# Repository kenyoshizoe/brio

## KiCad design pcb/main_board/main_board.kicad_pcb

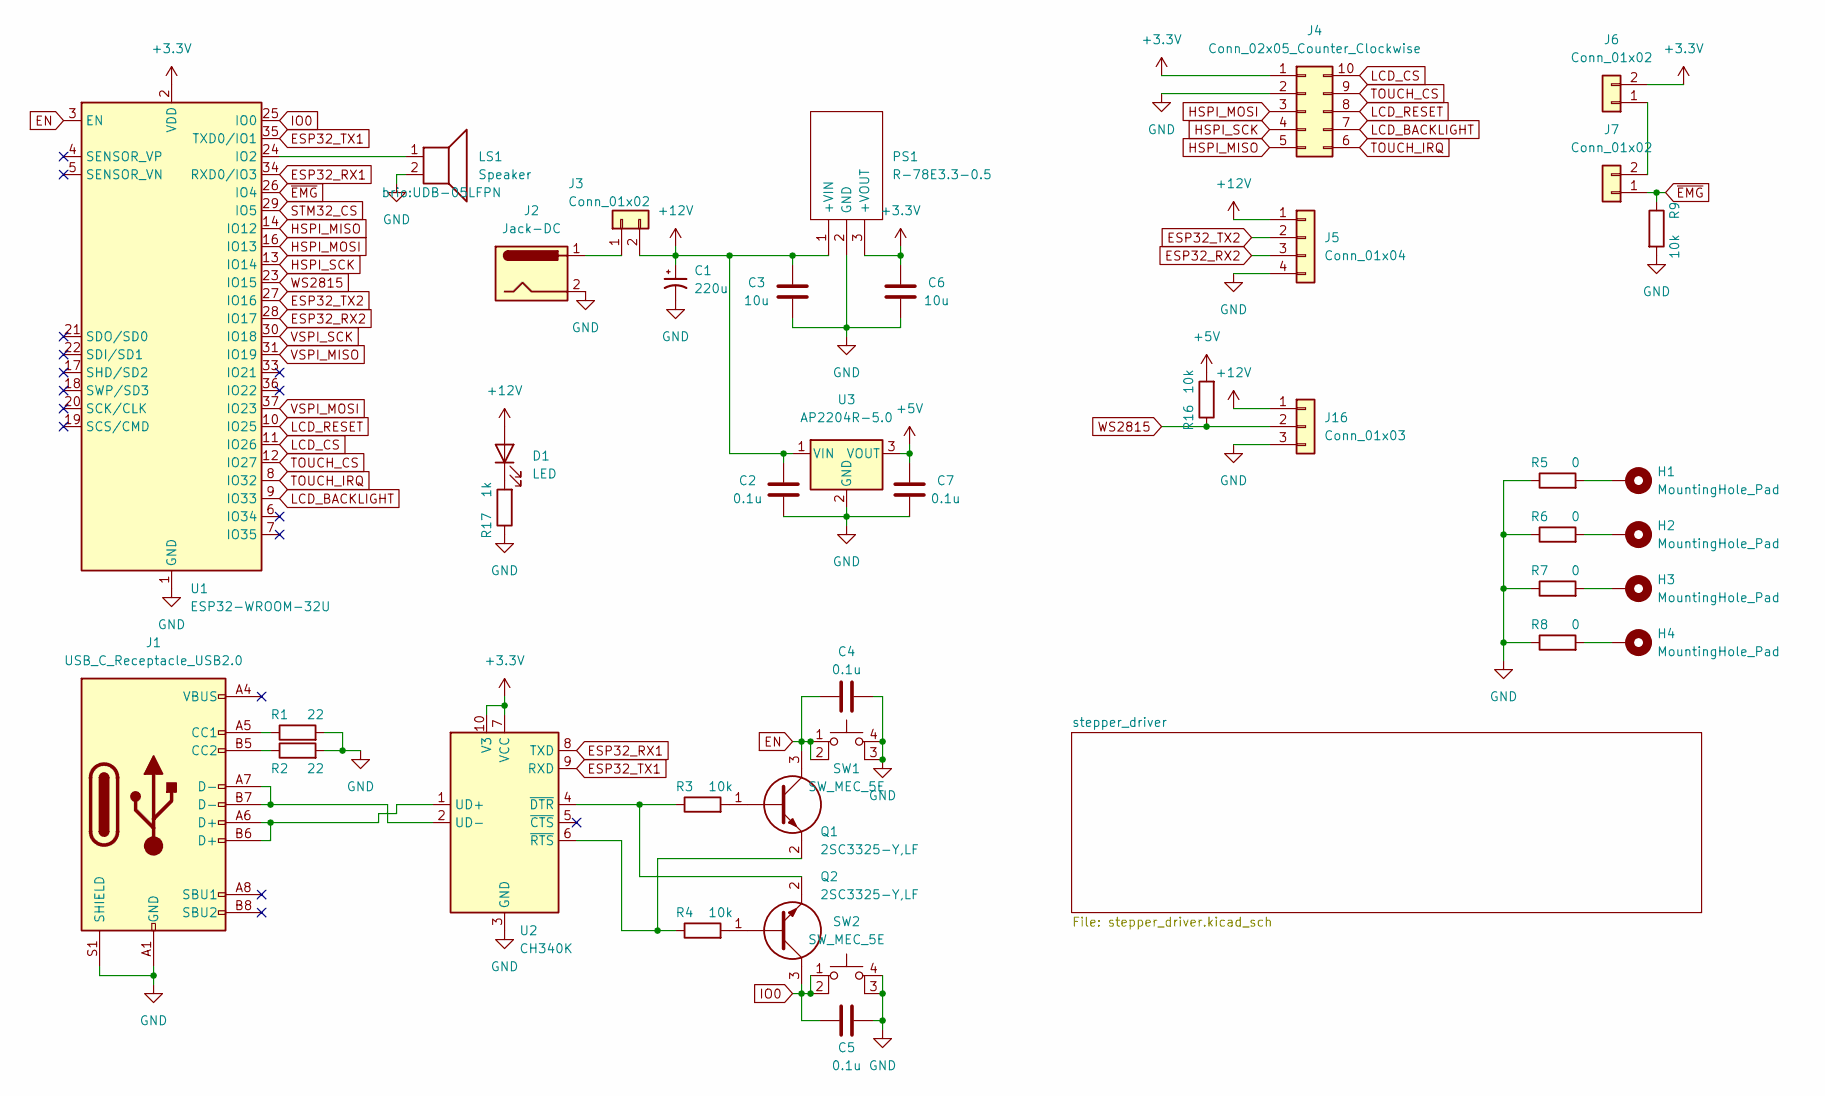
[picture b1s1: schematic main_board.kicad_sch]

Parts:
C1: 220u; CP_Elec_8x10
C2, C4, C5, C7: 0.1u; C_0603_1608Metric_Pad1.08x0.95mm_HandSolder
C3, C6: 10u; C_0603_1608Metric_Pad1.08x0.95mm_HandSolder
D1: LED; LED_0603_1608Metric_Pad1.05x0.95mm_HandSolder
H1, H2, H3, H4: MountingHole_Pad; MountingHole_3.2mm_M3_Pad_Via
J1: USB_C_Receptacle_USB2.0; USB_C_Receptacle_XKB_U262-16XN-4BVC11
J2: Jack-DC; 2DC-G213-D42
J3: Conn_01x02; JST_VH_B2P-VH_1x02_P3.96mm_Vertical
J4: Conn_02x05_Counter_Clockwise; PinHeader_2x05_P2.54mm_Vertical
J5: Conn_01x04; JST_PH_B4B-PH-K_1x04_P2.00mm_Vertical
J6: Conn_01x02; PinHeader_1x02_P2.54mm_Vertical
J7: Conn_01x02; PinHeader_1x02_P2.54mm_Horizontal
J16: Conn_01x03; JST_VH_B3P-VH_1x03_P3.96mm_Vertical
LS1: Speaker; UDB-05LFPN
PS1: R-78E3.3-0.5; R78E1205; Mouser Part Number 919-R-78E3.3-0.5
Q1, Q2: 2SC3325-Y,LF; 2SC3325YLF; Mouser Part Number 757-2SC3325-YLF
R1, R2: 22; R_0603_1608Metric_Pad0.98x0.95mm_HandSolder
R3, R4, R9, R16: 10k; R_0603_1608Metric_Pad0.98x0.95mm_HandSolder
R5, R6, R7, R8: 0; R_0603_1608Metric_Pad0.98x0.95mm_HandSolder
R17: 1k; R_0603_1608Metric_Pad0.98x0.95mm_HandSolder
SW1, SW2: SW_MEC_5E; SKRPABE010
U1: ESP32-WROOM-32U
U2: CH340K; SSOP-10_3.9x4.9mm_P1.00mm
U3: AP2204R-5.0; SOT-89-3

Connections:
+3.3V: C6.2, J4.1, J6.2, PS1.3 (+VOUT), U1.2 (VDD), U2.7 (VCC), U2.10 (V3); also elsewhere on the board
+5V: C7.2, R16.2, U3.3 (VOUT)
+12V: C1.1, C2.2, C3.2, D1.2 (A), J3.2, J5.1, J16.1, PS1.1 (+VIN), U3.1 (VIN); also elsewhere on the board
EN: C4.2, Q1.3, SW1.1, SW1.2, U1.3 (EN)
ESP32_RX1: U1.34 (RXD0/IO3), U2.8 (TXD)
ESP32_RX2: J5.3, U1.28 (IO17)
ESP32_TX1: U1.35 (TXD0/IO1), U2.9 (RXD)
ESP32_TX2: J5.2, U1.27 (IO16)
GND: C1.2, C2.1, C3.1, C4.1, C5.1, C6.1, C7.1, J1.A1 (GND), J1.A12 (GND), J1.B1 (GND), J1.B12 (GND), J1.S1 (SHIELD), J2.2, J4.2, J5.4, J16.3, LS1.2, PS1.2 (GND), R1.2, R2.2, R5.1, R6.1, R7.1, R8.1, R9.2, R17.1, SW1.3 (K), SW1.4 (A), SW2.3 (K), SW2.4 (A), U1.1 (GND), U1.15 (GND), U1.38 (GND), U1.39 (GND), U2.3 (GND), U3.2 (GND); also elsewhere on the board
HSPI_MISO: J4.5, U1.14 (IO12)
HSPI_MOSI: J4.3, U1.16 (IO13)
HSPI_SCK: J4.4, U1.13 (IO14)
IO0: C5.2, Q2.3, SW2.1, SW2.2, U1.25 (IO0)
LCD_BACKLIGHT: J4.7, U1.9 (IO33)
LCD_CS: J4.10, U1.11 (IO26)
LCD_RESET: J4.8, U1.10 (IO25)
unnamed: D1.1 (K), R17.2
unnamed: H1.1, R5.2
unnamed: H2.1, R6.2
unnamed: H3.1, R7.2
unnamed: H4.1, R8.2
unnamed: J1.A5 (CC1), R1.1
unnamed: J1.A6 (D+), J1.B6 (D+), U2.1 (UD+)
unnamed: J1.A7 (D-), J1.B7 (D-), U2.2 (UD-)
unnamed: J1.B5 (CC2), R2.1
unnamed: J2.1, J3.1
unnamed: J6.1, J7.2
unnamed: LS1.1, U1.24 (IO2)
unnamed: Q1.1, R3.2
unnamed: Q1.2, R4.1, U2.6 (~RTS)
unnamed: Q2.1, R4.2
unnamed: Q2.2, R3.1, U2.4 (~DTR)
STM32_CS: U1.29 (IO5); also elsewhere on the board
TOUCH_CS: J4.9, U1.12 (IO27)
TOUCH_IRQ: J4.6, U1.8 (IO32)
VSPI_MISO: U1.31 (IO19); also elsewhere on the board
VSPI_MOSI: U1.37 (IO23); also elsewhere on the board
VSPI_SCK: U1.30 (IO18); also elsewhere on the board
WS2815: J16.2, R16.1, U1.23 (IO15)
~EMG: J7.1, R9.1, U1.26 (IO4); also elsewhere on the board

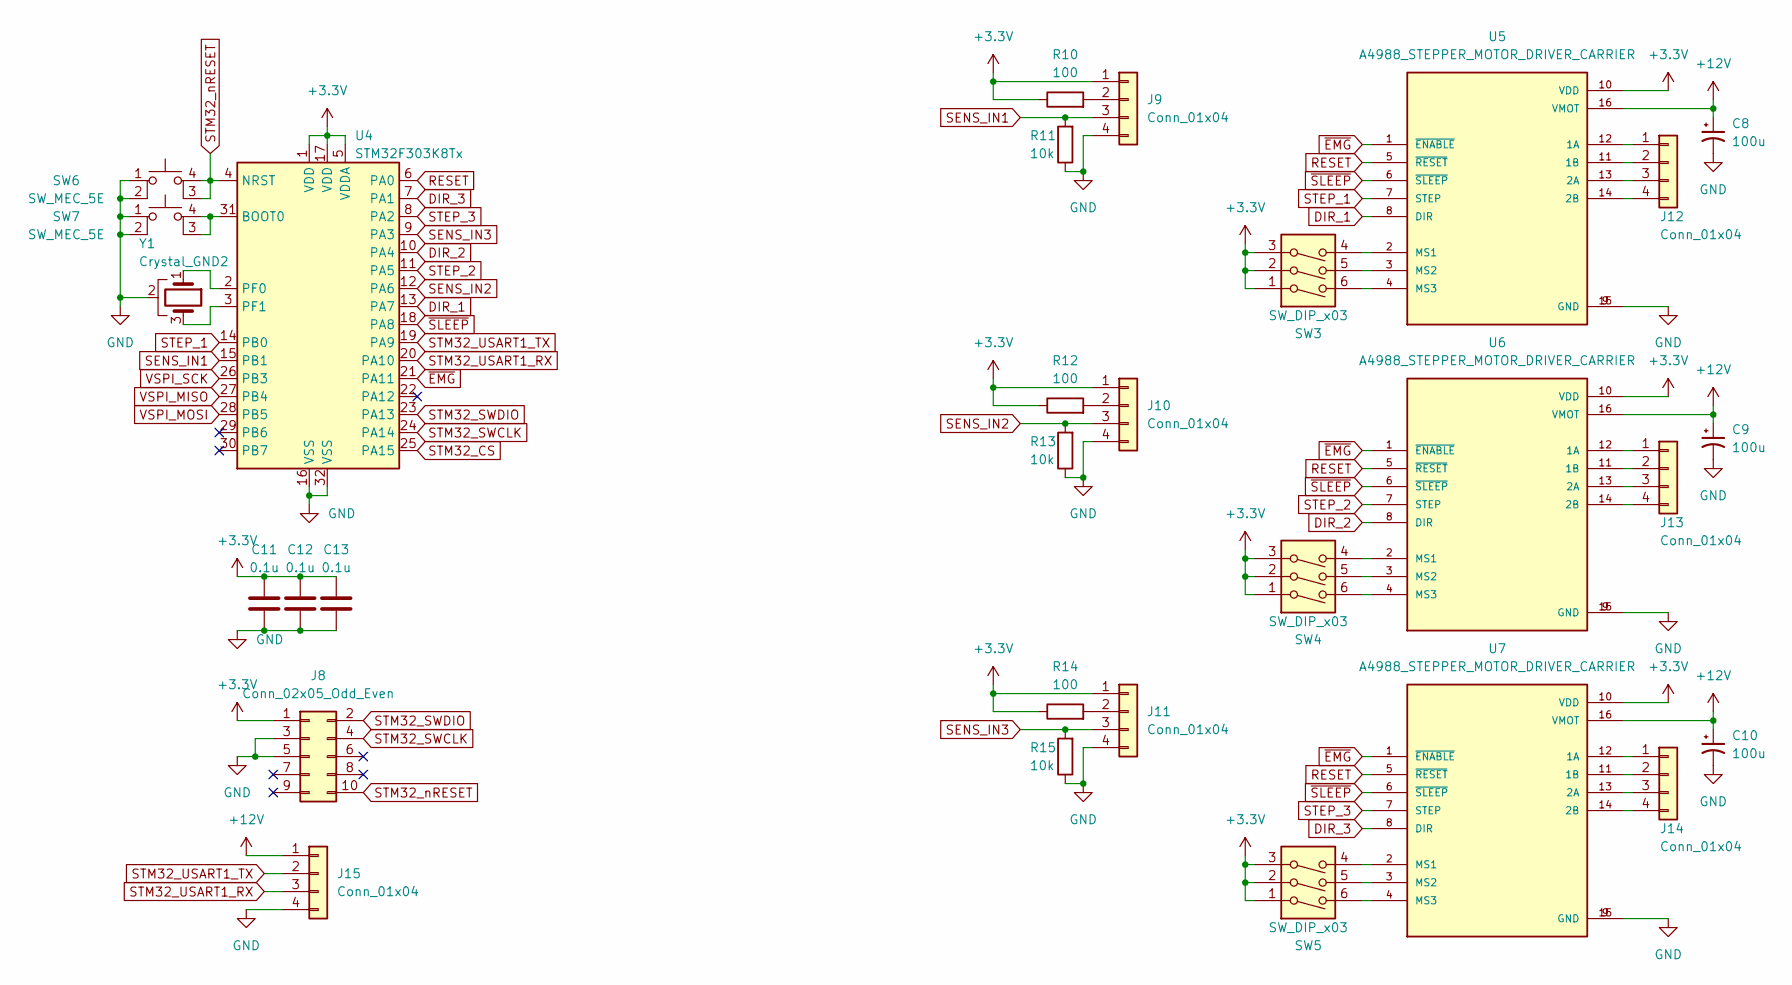
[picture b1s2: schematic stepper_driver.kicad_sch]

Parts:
C8, C9, C10: 100u; CP_Elec_6.3x5.7
C11, C12, C13: 0.1u; C_0603_1608Metric_Pad1.08x0.95mm_HandSolder
J8: Conn_02x05_Odd_Even; PinHeader_2x05_P1.27mm_Vertical
J9, J10, J11: Conn_01x04; JST_XH_B4B-XH-A_1x04_P2.50mm_Vertical
J12, J13, J14: Conn_01x04; JST_VH_B4P-VH_1x04_P3.96mm_Vertical
J15: Conn_01x04; JST_PH_B4B-PH-K_1x04_P2.00mm_Vertical
R10, R12, R14: 100; R_0603_1608Metric_Pad0.98x0.95mm_HandSolder
R11, R13, R15: 10k; R_0603_1608Metric_Pad0.98x0.95mm_HandSolder
SW3, SW4, SW5: SW_DIP_x03; SW_DIP_SPSTx03_Slide_6.7x9.18mm_W7.62mm_P2.54mm_LowProfile
SW6, SW7: SW_MEC_5E; SKRPABE010
U4: STM32F303K8Tx; LQFP-32_7x7mm_P0.8mm
U5, U6, U7: A4988_STEPPER_MOTOR_DRIVER_CARRIER; MODULE_A4988_STEPPER_MOTOR_DRIVER_CARRIER
Y1: Crystal_GND2; Resonator_SMD_Murata_CSTxExxV-3Pin_3.0x1.1mm_HandSoldering

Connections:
+3.3V: C11.2, C12.2, C13.2, J8.1, J9.1, J10.1, J11.1, R10.1, R12.1, R14.1, SW3.1, SW3.2, SW3.3, SW4.1, SW4.2, SW4.3, SW5.1, SW5.2, SW5.3, U4.1 (VDD), U4.5 (VDDA), U4.17 (VDD), U5.10 (VDD), U6.10 (VDD), U7.10 (VDD); also elsewhere on the board
+12V: C8.1, C9.1, C10.1, J15.1, U5.16 (VMOT), U6.16 (VMOT), U7.16 (VMOT); also elsewhere on the board
DIR_1: U4.13 (PA7), U5.8 (DIR)
DIR_2: U4.10 (PA4), U6.8 (DIR)
DIR_3: U4.7 (PA1), U7.8 (DIR)
GND: C8.2, C9.2, C10.2, C11.1, C12.1, C13.1, J8.3, J8.5, J9.4, J10.4, J11.4, J15.4, R11.1, R13.1, R15.1, SW6.1, SW6.2, SW7.1, SW7.2, U4.16 (VSS), U4.32 (VSS), U5.9 (GND), U5.15 (GND), U6.9 (GND), U6.15 (GND), U7.9 (GND), U7.15 (GND), Y1.2; also elsewhere on the board
unnamed: J9.2, R10.2
unnamed: J10.2, R12.2
unnamed: J11.2, R14.2
unnamed: J12.1, U5.12 (1A)
unnamed: J12.2, U5.11 (1B)
unnamed: J12.3, U5.13 (2A)
unnamed: J12.4, U5.14 (2B)
unnamed: J13.1, U6.12 (1A)
unnamed: J13.2, U6.11 (1B)
unnamed: J13.3, U6.13 (2A)
unnamed: J13.4, U6.14 (2B)
unnamed: J14.1, U7.12 (1A)
unnamed: J14.2, U7.11 (1B)
unnamed: J14.3, U7.13 (2A)
unnamed: J14.4, U7.14 (2B)
unnamed: SW3.4, U5.2 (MS1)
unnamed: SW3.5, U5.3 (MS2)
unnamed: SW3.6, U5.4 (MS3)
unnamed: SW4.4, U6.2 (MS1)
unnamed: SW4.5, U6.3 (MS2)
unnamed: SW4.6, U6.4 (MS3)
unnamed: SW5.4, U7.2 (MS1)
unnamed: SW5.5, U7.3 (MS2)
unnamed: SW5.6, U7.4 (MS3)
unnamed: SW7.3 (K), SW7.4 (A), U4.31 (BOOT0)
unnamed: U4.2 (PF0), Y1.1
unnamed: U4.3 (PF1), Y1.3
RESET: U4.6 (PA0), U5.5 (~RESET), U6.5 (~RESET), U7.5 (~RESET)
SENS_IN1: J9.3, R11.2, U4.15 (PB1)
SENS_IN2: J10.3, R13.2, U4.12 (PA6)
SENS_IN3: J11.3, R15.2, U4.9 (PA3)
STEP_1: U4.14 (PB0), U5.7 (STEP)
STEP_2: U4.11 (PA5), U6.7 (STEP)
STEP_3: U4.8 (PA2), U7.7 (STEP)
STM32_CS: U4.25 (PA15); also elsewhere on the board
STM32_SWCLK: J8.4, U4.24 (PA14)
STM32_SWDIO: J8.2, U4.23 (PA13)
STM32_USART1_RX: J15.3, U4.20 (PA10)
STM32_USART1_TX: J15.2, U4.19 (PA9)
STM32_nRESET: J8.10, SW6.3 (K), SW6.4 (A), U4.4 (NRST)
VSPI_MISO: U4.27 (PB4); also elsewhere on the board
VSPI_MOSI: U4.28 (PB5); also elsewhere on the board
VSPI_SCK: U4.26 (PB3); also elsewhere on the board
~EMG: U4.21 (PA11), U5.1 (~ENABLE), U6.1 (~ENABLE), U7.1 (~ENABLE); also elsewhere on the board
~SLEEP: U4.18 (PA8), U5.6 (~SLEEP), U6.6 (~SLEEP), U7.6 (~SLEEP)

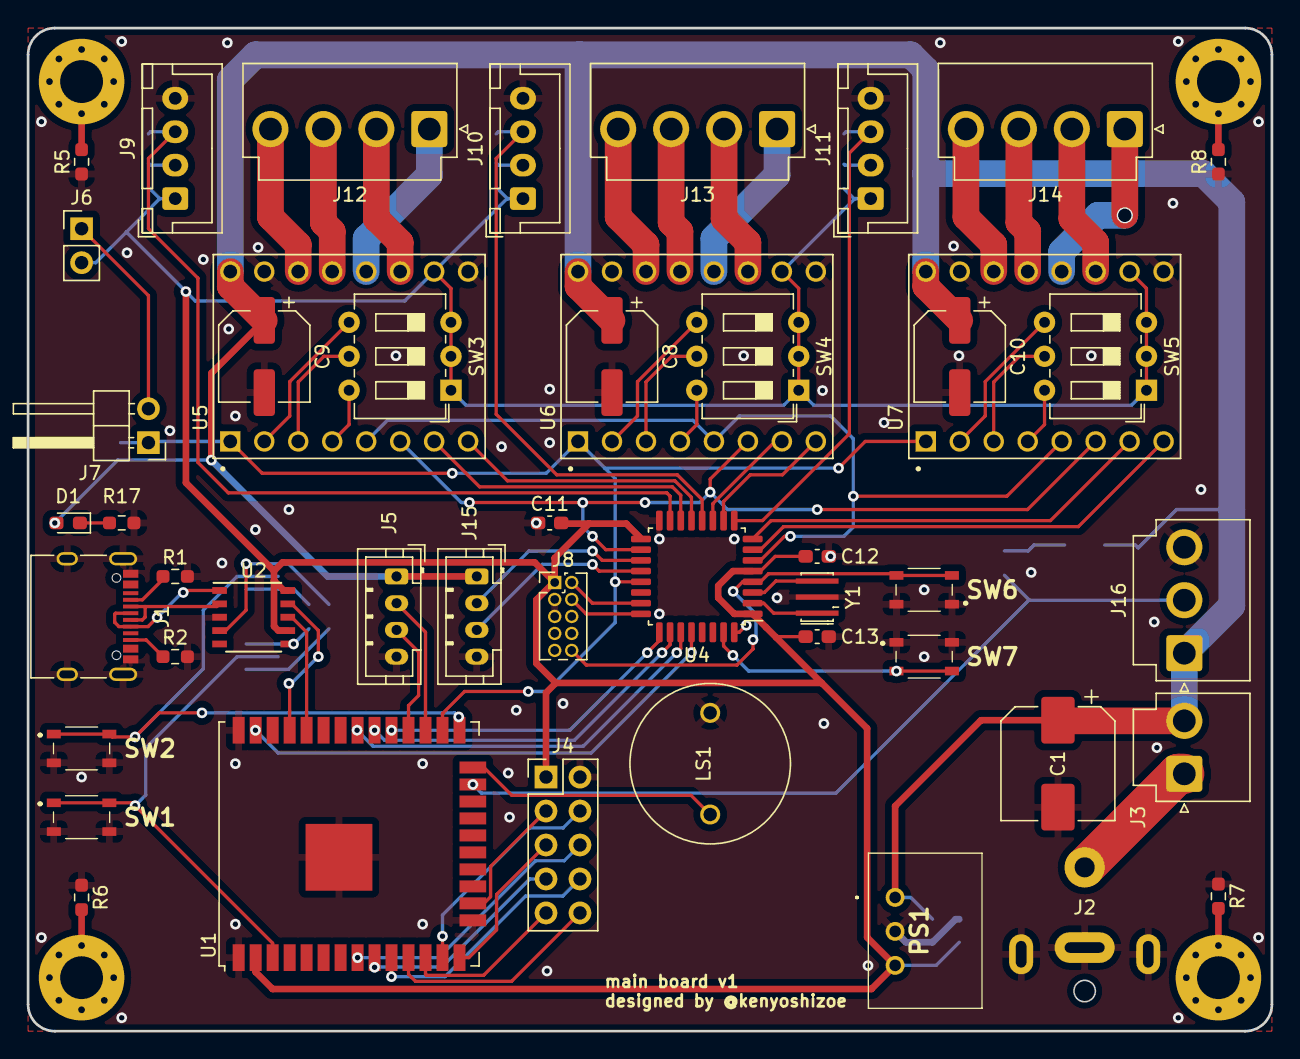
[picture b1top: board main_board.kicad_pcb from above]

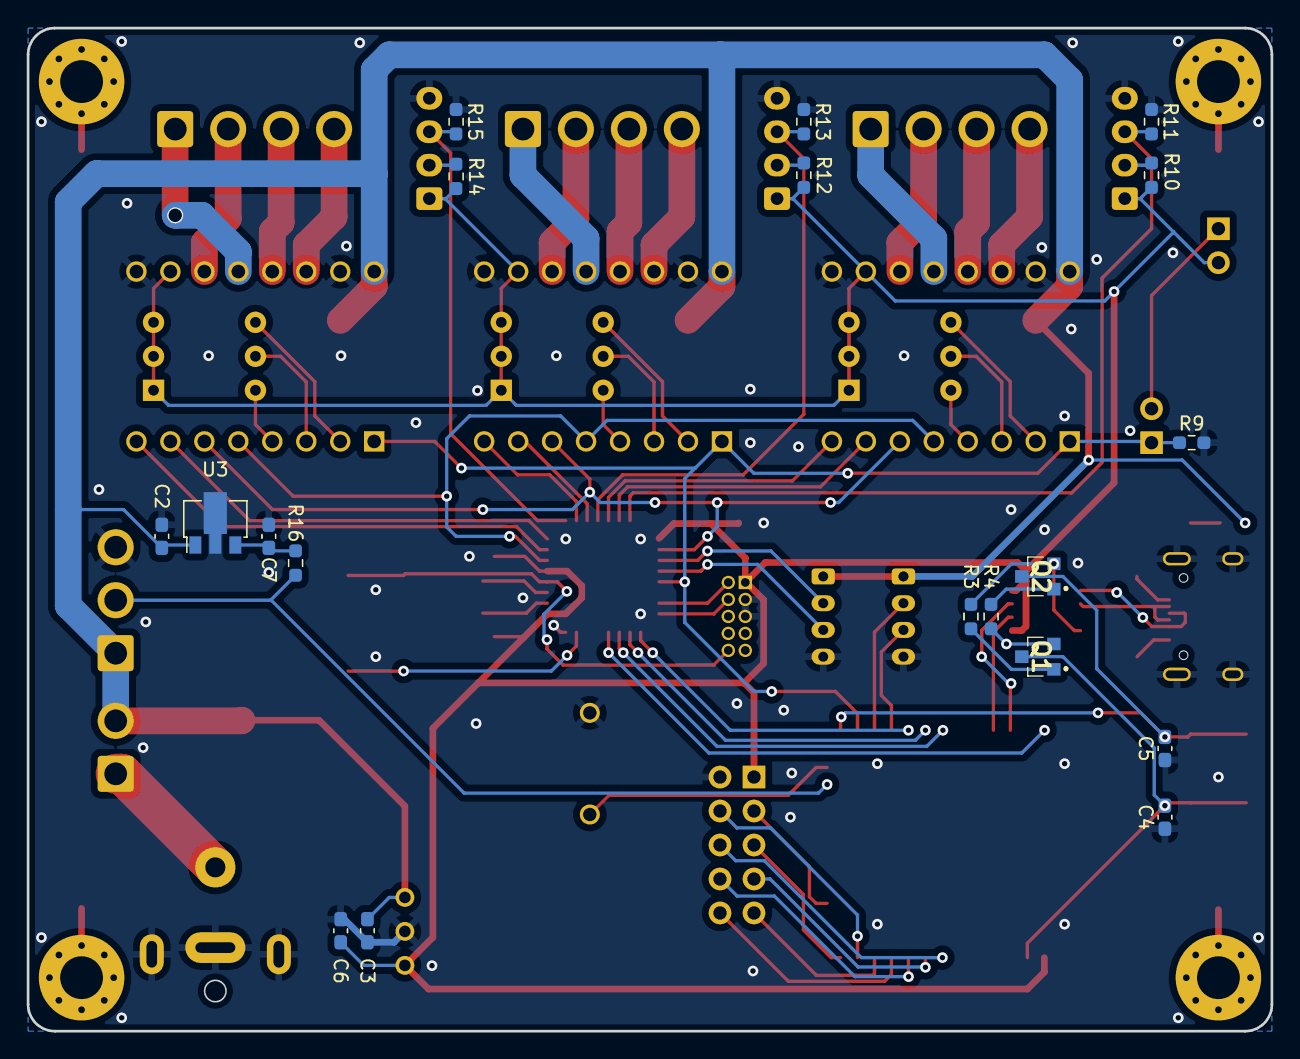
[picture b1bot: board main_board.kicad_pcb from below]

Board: 2 copper layers, 93.0 x 75.0 mm, 70 parts (19 on the bottom side), 83 nets.

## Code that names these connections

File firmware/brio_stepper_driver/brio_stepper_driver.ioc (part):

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Mcu.Name=STM32F303K(6-8)Tx
Mcu.Package=LQFP32
Mcu.UserName=STM32F303K8Tx
PA0.GPIOParameters=GPIO_Label
PA0.GPIO_Label=STEPPER_RESET
PA0.Signal=GPIO_Output
PA1.GPIOParameters=GPIO_Label
PA1.GPIO_Label=STEPPER3_DIR
PA1.Signal=GPIO_Output
PA10.Mode=Asynchronous
PA10.Signal=USART1_RX
PA11.GPIOParameters=GPIO_PuPd,GPIO_Label
PA11.GPIO_Label=STEPPER_EMG
PA11.GPIO_PuPd=GPIO_PULLDOWN
PA11.Signal=GPIO_Input
PA13.Mode=Serial_Wire
PA13.Signal=SYS_JTMS-SWDIO
PA14.Mode=Serial_Wire
PA14.Signal=SYS_JTCK-SWCLK
PA15.Mode=NSS_Signal_Hard_Input
PA15.Signal=SPI1_NSS
PA2.GPIOParameters=GPIO_Label
PA2.GPIO_Label=STEPPER3_STEP
PA2.Signal=S_TIM15_CH1
PA3.GPIOParameters=GPIO_Label
PA3.GPIO_Label=STEPPER3_SENS
PA3.Signal=GPIO_Input
PA4.GPIOParameters=GPIO_Label
PA4.GPIO_Label=STEPPER2_DIR
PA4.Signal=GPIO_Output
PA5.GPIOParameters=GPIO_Label
PA5.GPIO_Label=STEPPER2_STEP
PA5.Signal=S_TIM2_CH1_ETR
PA6.GPIOParameters=GPIO_Label
PA6.GPIO_Label=STEPPER2_SENS
PA6.Signal=GPIO_Input
PA7.GPIOParameters=GPIO_Label
PA7.GPIO_Label=STEPPER1_DIR
PA7.Signal=GPIO_Output
PA8.GPIOParameters=GPIO_Label
PA8.GPIO_Label=STEPPER_SLEEP
PA8.Signal=GPIO_Output
PA9.Mode=Asynchronous
PA9.Signal=USART1_TX
PB0.GPIOParameters=GPIO_Label
PB0.GPIO_Label=STEPPER1_STEP
PB0.Signal=S_TIM3_CH3
PB1.GPIOParameters=GPIO_Label
PB1.GPIO_Label=STEPPER1_SENS
PB1.Signal=GPIO_Input
PB3.Mode=Full_Duplex_Slave
PB3.Signal=SPI1_SCK
PB4.Mode=Full_Duplex_Slave
PB4.Signal=SPI1_MISO
PB5.Mode=Full_Duplex_Slave
PB5.Signal=SPI1_MOSI
PF0\ /\ OSC_IN.Mode=HSE-External-Oscillator
PF0\ /\ OSC_IN.Signal=RCC_OSC_IN
PF1\ /\ OSC_OUT.Mode=HSE-External-Oscillator
PF1\ /\ OSC_OUT.Signal=RCC_OSC_OUT
RCC.HSEPLLFreq_Value=16000000
RCC.HSE_VALUE=16000000
RCC.SYSCLKFreq_VALUE=8000000
board=custom

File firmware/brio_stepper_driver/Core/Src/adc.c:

/* USER CODE BEGIN Header */
/**
  ******************************************************************************
  * @file    adc.c
  * @brief   This file provides code for the configuration
  *          of the ADC instances.
  ******************************************************************************
  * @attention
  *
  * Copyright (c) 2023 STMicroelectronics.
  * All rights reserved.
  *
  * This software is licensed under terms that can be found in the LICENSE file
  * in the root directory of this software component.
  * If no LICENSE file comes with this software, it is provided AS-IS.
  *
  ******************************************************************************
  */
/* USER CODE END Header */
/* Includes ------------------------------------------------------------------*/
#include "adc.h"

/* USER CODE BEGIN 0 */

/* USER CODE END 0 */

ADC_HandleTypeDef hadc1;
ADC_HandleTypeDef hadc2;

/* ADC1 init function */
void MX_ADC1_Init(void)
{

  /* USER CODE BEGIN ADC1_Init 0 */

  /* USER CODE END ADC1_Init 0 */

  ADC_MultiModeTypeDef multimode = {0};
  ADC_ChannelConfTypeDef sConfig = {0};

  /* USER CODE BEGIN ADC1_Init 1 */

  /* USER CODE END ADC1_Init 1 */

  /** Common config
  */
  hadc1.Instance = ADC1;
  hadc1.Init.ClockPrescaler = ADC_CLOCK_ASYNC_DIV1;
  hadc1.Init.Resolution = ADC_RESOLUTION_12B;
  hadc1.Init.ScanConvMode = ADC_SCAN_DISABLE;
  hadc1.Init.ContinuousConvMode = DISABLE;
  hadc1.Init.DiscontinuousConvMode = DISABLE;
  hadc1.Init.ExternalTrigConvEdge = ADC_EXTERNALTRIGCONVEDGE_NONE;
  hadc1.Init.ExternalTrigConv = ADC_SOFTWARE_START;
  hadc1.Init.DataAlign = ADC_DATAALIGN_RIGHT;
  hadc1.Init.NbrOfConversion = 1;
  hadc1.Init.DMAContinuousRequests = DISABLE;
  hadc1.Init.EOCSelection = ADC_EOC_SINGLE_CONV;
  hadc1.Init.LowPowerAutoWait = DISABLE;
  hadc1.Init.Overrun = ADC_OVR_DATA_OVERWRITTEN;
  if (HAL_ADC_Init(&hadc1) != HAL_OK)
  {
    Error_Handler();
  }

  /** Configure the ADC multi-mode
  */
  multimode.Mode = ADC_MODE_INDEPENDENT;
  if (HAL_ADCEx_MultiModeConfigChannel(&hadc1, &multimode) != HAL_OK)
  {
    Error_Handler();
  }

  /** Configure Regular Channel
  */
  sConfig.Channel = ADC_CHANNEL_4;
  sConfig.Rank = ADC_REGULAR_RANK_1;
  sConfig.SingleDiff = ADC_SINGLE_ENDED;
  sConfig.SamplingTime = ADC_SAMPLETIME_1CYCLE_5;
  sConfig.OffsetNumber = ADC_OFFSET_NONE;
  sConfig.Offset = 0;
  if (HAL_ADC_ConfigChannel(&hadc1, &sConfig) != HAL_OK)
  {
    Error_Handler();
  }
  /* USER CODE BEGIN ADC1_Init 2 */

  /* USER CODE END ADC1_Init 2 */

}
/* ADC2 init function */
void MX_ADC2_Init(void)
{

  /* USER CODE BEGIN ADC2_Init 0 */

  /* USER CODE END ADC2_Init 0 */

  ADC_ChannelConfTypeDef sConfig = {0};

  /* USER CODE BEGIN ADC2_Init 1 */

  /* USER CODE END ADC2_Init 1 */

  /** Common config
  */
  hadc2.Instance = ADC2;
  hadc2.Init.ClockPrescaler = ADC_CLOCK_ASYNC_DIV1;
  hadc2.Init.Resolution = ADC_RESOLUTION_12B;
  hadc2.Init.ScanConvMode = ADC_SCAN_DISABLE;
  hadc2.Init.ContinuousConvMode = DISABLE;
  hadc2.Init.DiscontinuousConvMode = DISABLE;
  hadc2.Init.ExternalTrigConvEdge = ADC_EXTERNALTRIGCONVEDGE_NONE;
  hadc2.Init.ExternalTrigConv = ADC_SOFTWARE_START;
  hadc2.Init.DataAlign = ADC_DATAALIGN_RIGHT;
  hadc2.Init.NbrOfConversion = 1;
  hadc2.Init.DMAContinuousRequests = DISABLE;
  hadc2.Init.EOCSelection = ADC_EOC_SINGLE_CONV;
  hadc2.Init.LowPowerAutoWait = DISABLE;
  hadc2.Init.Overrun = ADC_OVR_DATA_OVERWRITTEN;
  if (HAL_ADC_Init(&hadc2) != HAL_OK)
  {
    Error_Handler();
  }

  /** Configure Regular Channel
  */
  sConfig.Channel = ADC_CHANNEL_3;
  sConfig.Rank = ADC_REGULAR_RANK_1;
  sConfig.SingleDiff = ADC_SINGLE_ENDED;
  sConfig.SamplingTime = ADC_SAMPLETIME_1CYCLE_5;
  sConfig.OffsetNumber = ADC_OFFSET_NONE;
  sConfig.Offset = 0;
  if (HAL_ADC_ConfigChannel(&hadc2, &sConfig) != HAL_OK)
  {
    Error_Handler();
  }
  /* USER CODE BEGIN ADC2_Init 2 */

  /* USER CODE END ADC2_Init 2 */

}

static uint32_t HAL_RCC_ADC12_CLK_ENABLED=0;

void HAL_ADC_MspInit(ADC_HandleTypeDef* adcHandle)
{

  GPIO_InitTypeDef GPIO_InitStruct = {0};
  if(adcHandle->Instance==ADC1)
  {
  /* USER CODE BEGIN ADC1_MspInit 0 */

  /* USER CODE END ADC1_MspInit 0 */
    /* ADC1 clock enable */
    HAL_RCC_ADC12_CLK_ENABLED++;
    if(HAL_RCC_ADC12_CLK_ENABLED==1){
      __HAL_RCC_ADC12_CLK_ENABLE();
    }

    __HAL_RCC_GPIOA_CLK_ENABLE();
    __HAL_RCC_GPIOB_CLK_ENABLE();
    /**ADC1 GPIO Configuration
    PA3     ------> ADC1_IN4
    PB1     ------> ADC1_IN12
    */
    GPIO_InitStruct.Pin = sens_in3_Pin;
    GPIO_InitStruct.Mode = GPIO_MODE_ANALOG;
    GPIO_InitStruct.Pull = GPIO_NOPULL;
    HAL_GPIO_Init(sens_in3_GPIO_Port, &GPIO_InitStruct);

    GPIO_InitStruct.Pin = sens_in1_Pin;
    GPIO_InitStruct.Mode = GPIO_MODE_ANALOG;
    GPIO_InitStruct.Pull = GPIO_NOPULL;
    HAL_GPIO_Init(sens_in1_GPIO_Port, &GPIO_InitStruct);

  /* USER CODE BEGIN ADC1_MspInit 1 */

  /* USER CODE END ADC1_MspInit 1 */
  }
  else if(adcHandle->Instance==ADC2)
  {
  /* USER CODE BEGIN ADC2_MspInit 0 */

  /* USER CODE END ADC2_MspInit 0 */
    /* ADC2 clock enable */
    HAL_RCC_ADC12_CLK_ENABLED++;
    if(HAL_RCC_ADC12_CLK_ENABLED==1){
      __HAL_RCC_ADC12_CLK_ENABLE();
    }

    __HAL_RCC_GPIOA_CLK_ENABLE();
    /**ADC2 GPIO Configuration
    PA6     ------> ADC2_IN3
    */
    GPIO_InitStruct.Pin = sens_in2_Pin;
    GPIO_InitStruct.Mode = GPIO_MODE_ANALOG;
    GPIO_InitStruct.Pull = GPIO_NOPULL;
    HAL_GPIO_Init(sens_in2_GPIO_Port, &GPIO_InitStruct);

  /* USER CODE BEGIN ADC2_MspInit 1 */

  /* USER CODE END ADC2_MspInit 1 */
  }
}

void HAL_ADC_MspDeInit(ADC_HandleTypeDef* adcHandle)
{

  if(adcHandle->Instance==ADC1)
  {
  /* USER CODE BEGIN ADC1_MspDeInit 0 */

  /* USER CODE END ADC1_MspDeInit 0 */
    /* Peripheral clock disable */
    HAL_RCC_ADC12_CLK_ENABLED--;
    if(HAL_RCC_ADC12_CLK_ENABLED==0){
      __HAL_RCC_ADC12_CLK_DISABLE();
    }

    /**ADC1 GPIO Configuration
    PA3     ------> ADC1_IN4
    PB1     ------> ADC1_IN12
    */
    HAL_GPIO_DeInit(sens_in3_GPIO_Port, sens_in3_Pin);

    HAL_GPIO_DeInit(sens_in1_GPIO_Port, sens_in1_Pin);

  /* USER CODE BEGIN ADC1_MspDeInit 1 */

  /* USER CODE END ADC1_MspDeInit 1 */
  }
  else if(adcHandle->Instance==ADC2)
  {
  /* USER CODE BEGIN ADC2_MspDeInit 0 */

  /* USER CODE END ADC2_MspDeInit 0 */
    /* Peripheral clock disable */
    HAL_RCC_ADC12_CLK_ENABLED--;
    if(HAL_RCC_ADC12_CLK_ENABLED==0){
      __HAL_RCC_ADC12_CLK_DISABLE();
    }

    /**ADC2 GPIO Configuration
    PA6     ------> ADC2_IN3
    */
    HAL_GPIO_DeInit(sens_in2_GPIO_Port, sens_in2_Pin);

  /* USER CODE BEGIN ADC2_MspDeInit 1 */

  /* USER CODE END ADC2_MspDeInit 1 */
  }
}

/* USER CODE BEGIN 1 */

/* USER CODE END 1 */

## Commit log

2023-04-09 :tada: generate project
2023-04-16 🎉 add main_board pcb
2023-04-16 🎉 generate project
2023-04-16 🐛 fix a4988 lib
2023-04-16 🐛 minor fix
2023-04-19 ✨ add pin_assign
2023-04-19 ✨ add init buzzer
2023-04-23 ✨ set pin user label
2023-04-23 ➕ add SEGGER-RTT as submodule
2023-04-23 🔧 add build in .gitsubmodule
2023-04-23 🔧 configure .vscode
2023-04-23 ✨ change pin setting adc -> gpio input
2023-04-23 ✨ enable tim
2023-04-23 ✨ configure makefile for cpp
2023-04-23 🐛 fix makefile
2023-04-24 ✨ configure pwm settings
2023-04-24 ✨ configure tim settings
2023-04-24 🎉 add a4988 class
2023-04-24 🎉 add app.h/cc
2023-04-24 ➕ c++17
2023-04-24 ♻️ refuctor
2023-04-24 ✨ change app
2023-04-24 🐛 fix boundary process
2023-04-25 :wrench: add volatile
2023-04-25 :sparkles: add pulse2rad / rad2pulse
2023-04-25 :recycle: refuctor update
2023-04-25 :bug: fix set accel unit
2023-04-25 :sparkles: add default speed
2023-04-25 :sparkles: add GetAngle()
2023-04-25 :sparkles: add MoveTo()
2023-04-25 :sparkles: add min step
2023-04-25 :recycle: move kPI other file
2023-04-25 ➕ add etl as submodule
2023-04-25 ✨ add etl include in makefile
2023-04-25 🐛 fix speed set
2023-04-27 :tada: add brio_description
2023-04-27 🎉 enable iwdg
2023-04-27 :rocket: parameter tuning
2023-04-27 :recycle: change file extension
2023-04-27 :sparkles: add buzzer class
2023-04-28 :sparkles: change cubemx spi settting
2023-04-28 :tada: add stepper driver receive cmd process
2023-04-28 :recycle: change directory structure
2023-04-28 :heavy_plus_sign: add etl library to brio_main
2023-04-28 :tada: add StepperDriver class to main
2023-04-28 :sparkles: add timer callback communication with stepper_driver
2023-04-28 :tada: add crc check
2023-04-29 :wastebasket: delete crc
2023-04-29 :bug: fix stepper driver class
2023-04-29 :wrench: change a4988 class to adapt continuous cmd
2023-06-07 :heavy_plus_sign: add nanopb
2023-06-07 :sparkles: add proto
2023-06-07 :sparkles: add cobs
2023-06-07 :sparkles: add buzzer.Play()
2023-06-07 :tada: add brio_driver package
2023-06-08 :wrench: add package brio; to proto file
2023-06-08 :tada: add process to communicate with pc via uart
2023-06-08 :bug: minor fix cobs
2023-06-08 :sparkles: add thread finish process
2023-06-08 :sparkles: add send func
2023-06-08 :bug: fix position / velocity coord
2023-06-08 :tada: add brio_msgs package
2023-06-08 :sparkles: add Cartesian Command service
2023-06-09 :sparkles: add tip_link to urdf
2023-06-09 :recycle: refuctor open port process
2023-06-09 :sparkles: add brio_msgs dependency
